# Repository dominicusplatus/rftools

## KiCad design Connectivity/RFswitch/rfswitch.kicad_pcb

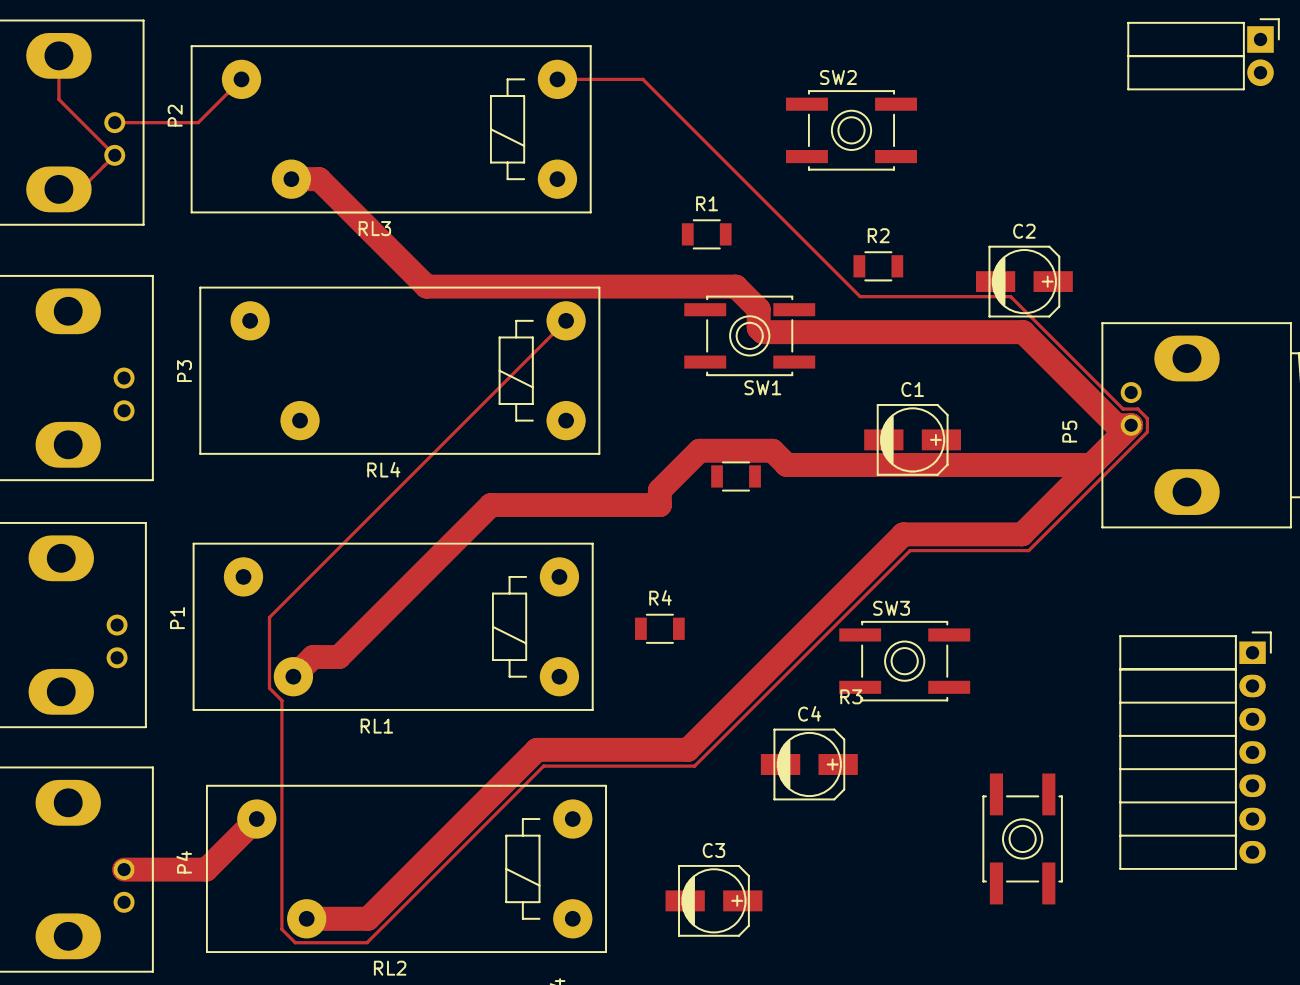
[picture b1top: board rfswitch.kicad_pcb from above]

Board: 2 copper layers, 23 parts (0 on the bottom side), 18 nets.

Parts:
C1, C2, C3, C4: CP; c_elec_5x5.3
P1, P2, P3, P4, P5: BNC; BNC_Socket_TYCO-AMP
P6: CONN_01X02; Socket_Strip_Angled_1x02
R1, R2, R3, R4: R; R_1206
RL1, RL2, RL3, RL4: RM50-xx21; Relay_SPDT_Schrack-RP-II-1_RM3-5mm
SW1, SW2, SW3, SW4: SW_PUSH; SW_SPST_EVQP0
U1: LT1129CS8; Socket_Strip_Angled_1x07

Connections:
+12V: P6.2, U1.5
GND: C1.2, C3.2, C4.2, P6.1, U1.3, U1.7
unnamed: C1.1, R1.1, RL1.A1
unnamed: C2.1, R2.1, RL3.A1
unnamed: C3.1, R3.1, RL4.A1
unnamed: P1.1, RL1.14
unnamed: P1.2, P2.2, P3.2, P4.2, P5.2
unnamed: P2.1, RL3.14
unnamed: P3.1, RL4.14
unnamed: P4.1, RL2.14
unnamed: P5.1, RL1.11, RL2.11, RL3.11, RL4.11
unnamed: R1.2, SW1.1
unnamed: R2.2, SW2.1
unnamed: R3.2, SW3.2
unnamed: R4.1, RL2.A1
unnamed: R4.2, SW4.1
unnamed: RL1.A2, RL2.A2, RL3.A2, RL4.A2
unnamed: SW4.2, U1.1

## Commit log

2016-02-23 initial
2016-02-23 initial struct lpda and switch board
2016-02-25 initial sch and layout
2016-02-28 initial proj struct, bench pcb sch initial eagle, import matlab sims
2016-02-29 bench trx matlab global models initially, blocks models
2016-03-08 trx model sim matlab initial
2016-03-09 mixer building blocks
2016-06-05 redo struct
2016-06-12 ham trx workspace project altium intial sch
2016-06-25 filter calculation formules, normalized references, bandpass 1-7 order
2016-06-25 simulate filter bandpass 3 order 6m band
2016-06-26 matlab sim trx, hartley, ssb
2016-06-26 10 band filter calc + sim 3rd order
